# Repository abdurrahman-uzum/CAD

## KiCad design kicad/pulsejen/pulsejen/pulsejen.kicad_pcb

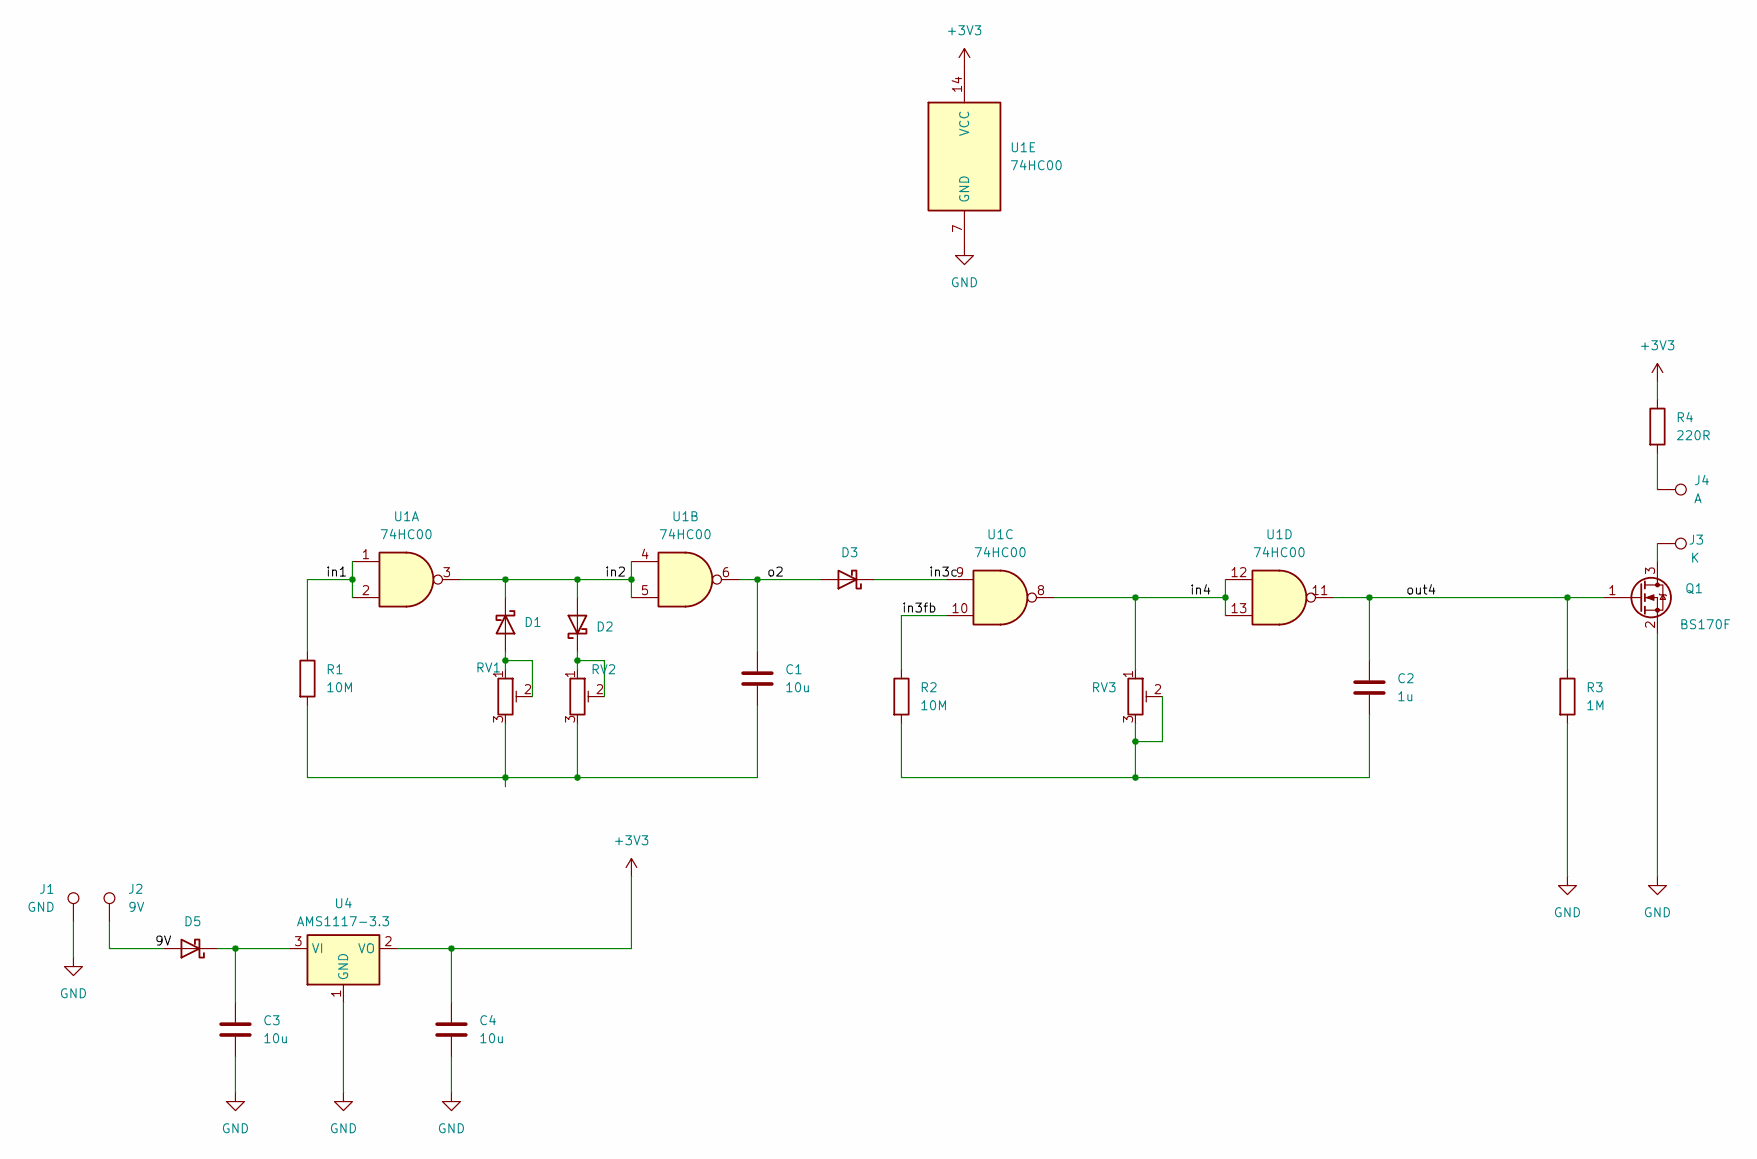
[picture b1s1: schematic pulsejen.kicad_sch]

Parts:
C1, C3, C4: 10u; C_0805_2012Metric_Pad1.18x1.45mm_HandSolder
C2: 1u; C_0805_2012Metric_Pad1.18x1.45mm_HandSolder
D1, D2, D3, D5: D_Schottky; D_SOD-123
J1: GND; TestPoint_Pad_2.0x2.0mm
J2: 9V; TestPoint_Pad_D2.0mm
J3: K; TestPoint_Pad_2.0x2.0mm
J4: A; TestPoint_Pad_D2.0mm
Q1: BS170F; SOT-23
R1, R2: 10M; R_0805_2012Metric_Pad1.20x1.40mm_HandSolder
R3: 1M; R_0805_2012Metric_Pad1.20x1.40mm_HandSolder
R4: 220R; R_1206_3216Metric_Pad1.30x1.75mm_HandSolder
RV1, RV2, RV3: R_Potentiometer_Trim; 10x10_smd
U1: 74HC00; SOIC-14_3.9x8.7mm_P1.27mm
U4: AMS1117-3.3; SOT-223-3_TabPin2

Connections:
+3V3: C4.1, R4.1, U1.14 (VCC), U4.2 (VO)
/9V: D5.2 (A), J2.1
/in1: R1.1, U1.1, U1.2
/in2: D1.1 (K), D2.2 (A), U1.3, U1.4, U1.5
/in3c: D3.1 (K), U1.9
/in3fb: R2.1, U1.10
/in4: RV3.1, U1.8, U1.12, U1.13
/o2: C1.1, D3.2 (A), U1.6
/out4: C2.1, Q1.1 (G), R3.1, U1.11
GND: C3.2, C4.2, J1.1, Q1.2 (S), R3.2, U1.7 (GND), U4.1 (GND)
unnamed: C1.2, R1.2, RV1.3, RV2.3
unnamed: C2.2, R2.2, RV3.2, RV3.3
unnamed: D1.2 (A), RV1.1, RV1.2
unnamed: D2.1 (K), RV2.1, RV2.2
unnamed: C3.1, D5.1 (K), U4.3 (VI)
unnamed: J4.1, R4.2
unnamed: J3.1, Q1.3 (D)

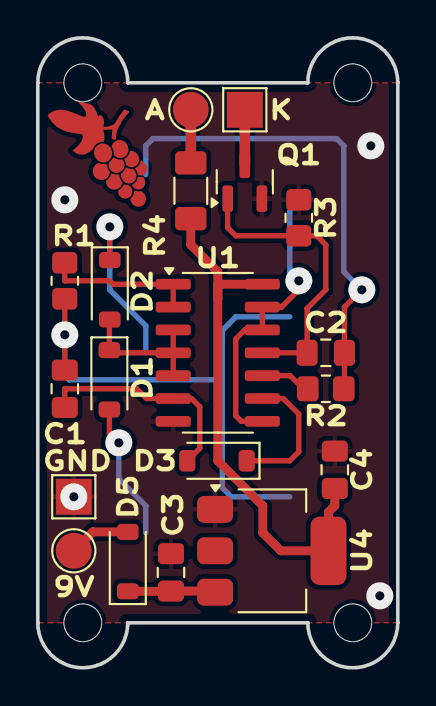
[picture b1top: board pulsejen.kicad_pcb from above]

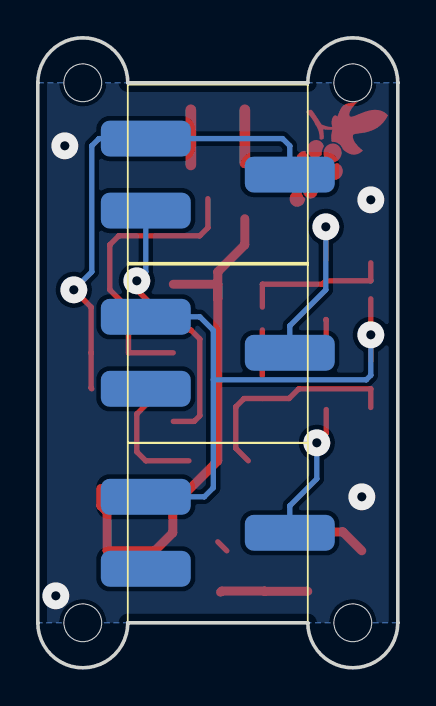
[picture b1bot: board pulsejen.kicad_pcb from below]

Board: 2 copper layers, 20.0 x 35.0 mm, 22 parts (3 on the bottom side), 17 nets.

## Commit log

2022-05-16 Backup
2023-03-12 110323
2023-03-27 280323
2024-03-15 150324
2024-05-26 260524
